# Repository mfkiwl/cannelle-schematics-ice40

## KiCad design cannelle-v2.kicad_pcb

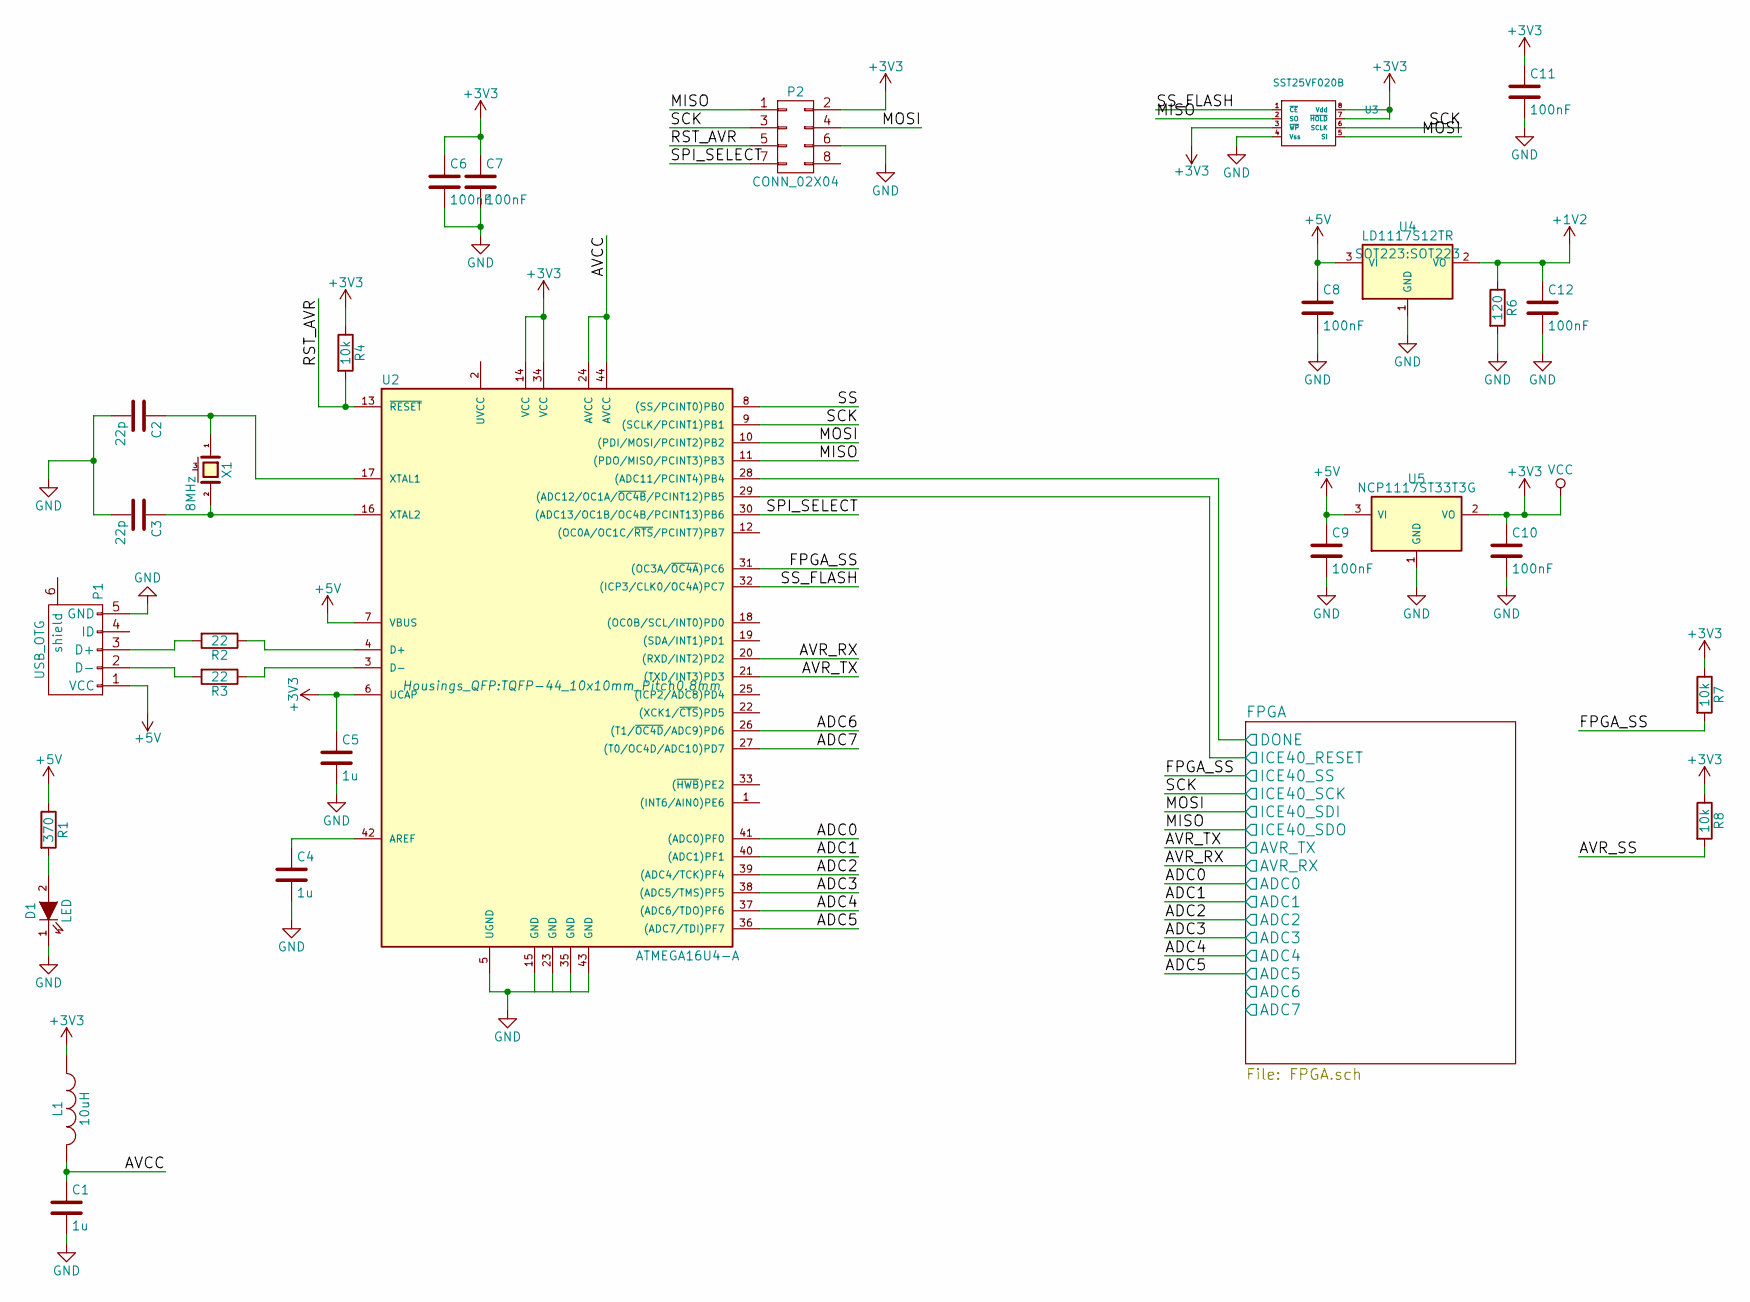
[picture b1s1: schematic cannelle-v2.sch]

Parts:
C1, C4, C5: 1u; C_0402
C2, C3: 22p; C_0402
C6, C7, C8, C9, C10, C11, C12: 100nF; C_0402
D1: LED; C_0603_HandSoldering
L1: 10uH; Neosid_Inductor_SM-NE29_SMD1008
P1: USB_OTG; USB_Mini-B
P2: CONN_02X04; Socket_Strip_Straight_2x04
R1: 370; R_0402
R2, R3: 22; R_0402
R4, R7, R8: 10k; R_0402
R6: 120; R_0402
U2: ATMEGA16U4-A; TQFP-44_10x10mm_Pitch0.8mm
U3: SST25VF020B; SOIC-8-N
U4: LD1117S12TR; SOT223
U5: NCP1117ST33T3G; SOT223
X1: 8MHz; Crystal_HC49-SD_SMD

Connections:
+1V2: C12.1, R6.1, U4.2 (VO); also elsewhere on the board
+3V3: C5.1, C6.1, C7.1, C10.1, C11.1, L1.1, P2.2, R4.1, R7.1, R8.1, U2.6 (UCAP), U2.14 (VCC), U2.34 (VCC), U3.3 (~WP), U3.7 (~HOLD), U3.8 (Vdd), U5.2 (VO); also elsewhere on the board
+5V: C8.1, C9.1, P1.1 (VCC), R1.1, U2.7 (VBUS), U4.3 (VI), U5.3 (VI); also elsewhere on the board
/ADC6: U2.26 ((T1/~OC4D~/ADC9)PD6)
/ADC7: U2.27 ((T0/OC4D/ADC10)PD7)
/AVCC: C1.1, L1.2, U2.24 (AVCC), U2.44 (AVCC)
/AVR_SS: R8.2
/FPGA/ADC0: U2.41 ((ADC0)PF0); also elsewhere on the board
/FPGA/ADC1: U2.40 ((ADC1)PF1); also elsewhere on the board
/FPGA/ADC2: U2.39 ((ADC4/TCK)PF4); also elsewhere on the board
/FPGA/ADC3: U2.38 ((ADC5/TMS)PF5); also elsewhere on the board
/FPGA/ADC4: U2.37 ((ADC6/TDO)PF6); also elsewhere on the board
/FPGA/ADC5: U2.36 ((ADC7/TDI)PF7); also elsewhere on the board
/FPGA/AVR_RX: U2.20 ((RXD/INT2)PD2); also elsewhere on the board
/FPGA/AVR_TX: U2.21 ((TXD/INT3)PD3); also elsewhere on the board
/FPGA/DONE: U2.28 ((ADC11/PCINT4)PB4); also elsewhere on the board
/FPGA/ICE40_RESET: U2.29 ((ADC12/OC1A/~OC4B~/PCINT12)PB5); also elsewhere on the board
/FPGA/ICE40_SCK: P2.3, U2.9 ((SCLK/PCINT1)PB1), U3.6 (SCLK); also elsewhere on the board
/FPGA/ICE40_SDI: P2.4, U2.10 ((PDI/MOSI/PCINT2)PB2), U3.5 (SI); also elsewhere on the board
/FPGA/ICE40_SDO: P2.1, U2.11 ((PDO/MISO/PCINT3)PB3), U3.2 (SO); also elsewhere on the board
/FPGA/ICE40_SS: R7.2, U2.31 ((OC3A/~OC4A~)PC6); also elsewhere on the board
/SPI_SELECT: P2.7, U2.30 ((ADC13/OC1B/OC4B/PCINT13)PB6)
/SS: U2.8 ((SS/PCINT0)PB0)
/SS_FLASH: U2.32 ((ICP3/CLK0/OC4A)PC7), U3.1 (~CE)
GND: C1.2, C2.2, C3.2, C4.2, C5.2, C6.2, C7.2, C8.2, C9.2, C10.2, C11.2, C12.2, D1.1 (K), P1.5 (GND), P2.6, R6.2, U2.5 (UGND), U2.43 (GND), U3.4 (Vss), U4.1 (GND), U5.1 (GND); also elsewhere on the board
unnamed: C2.1, U2.17 (XTAL1), X1.1
unnamed: C3.1, U2.16 (XTAL2), X1.2
unnamed: C4.1, U2.42 (AREF)
unnamed: D1.2 (A), R1.2
unnamed: P1.2 (D-), R3.2
unnamed: P1.3 (D+), R2.2
unnamed: R2.1, U2.4 (D+)
unnamed: R3.1, U2.3 (D-)

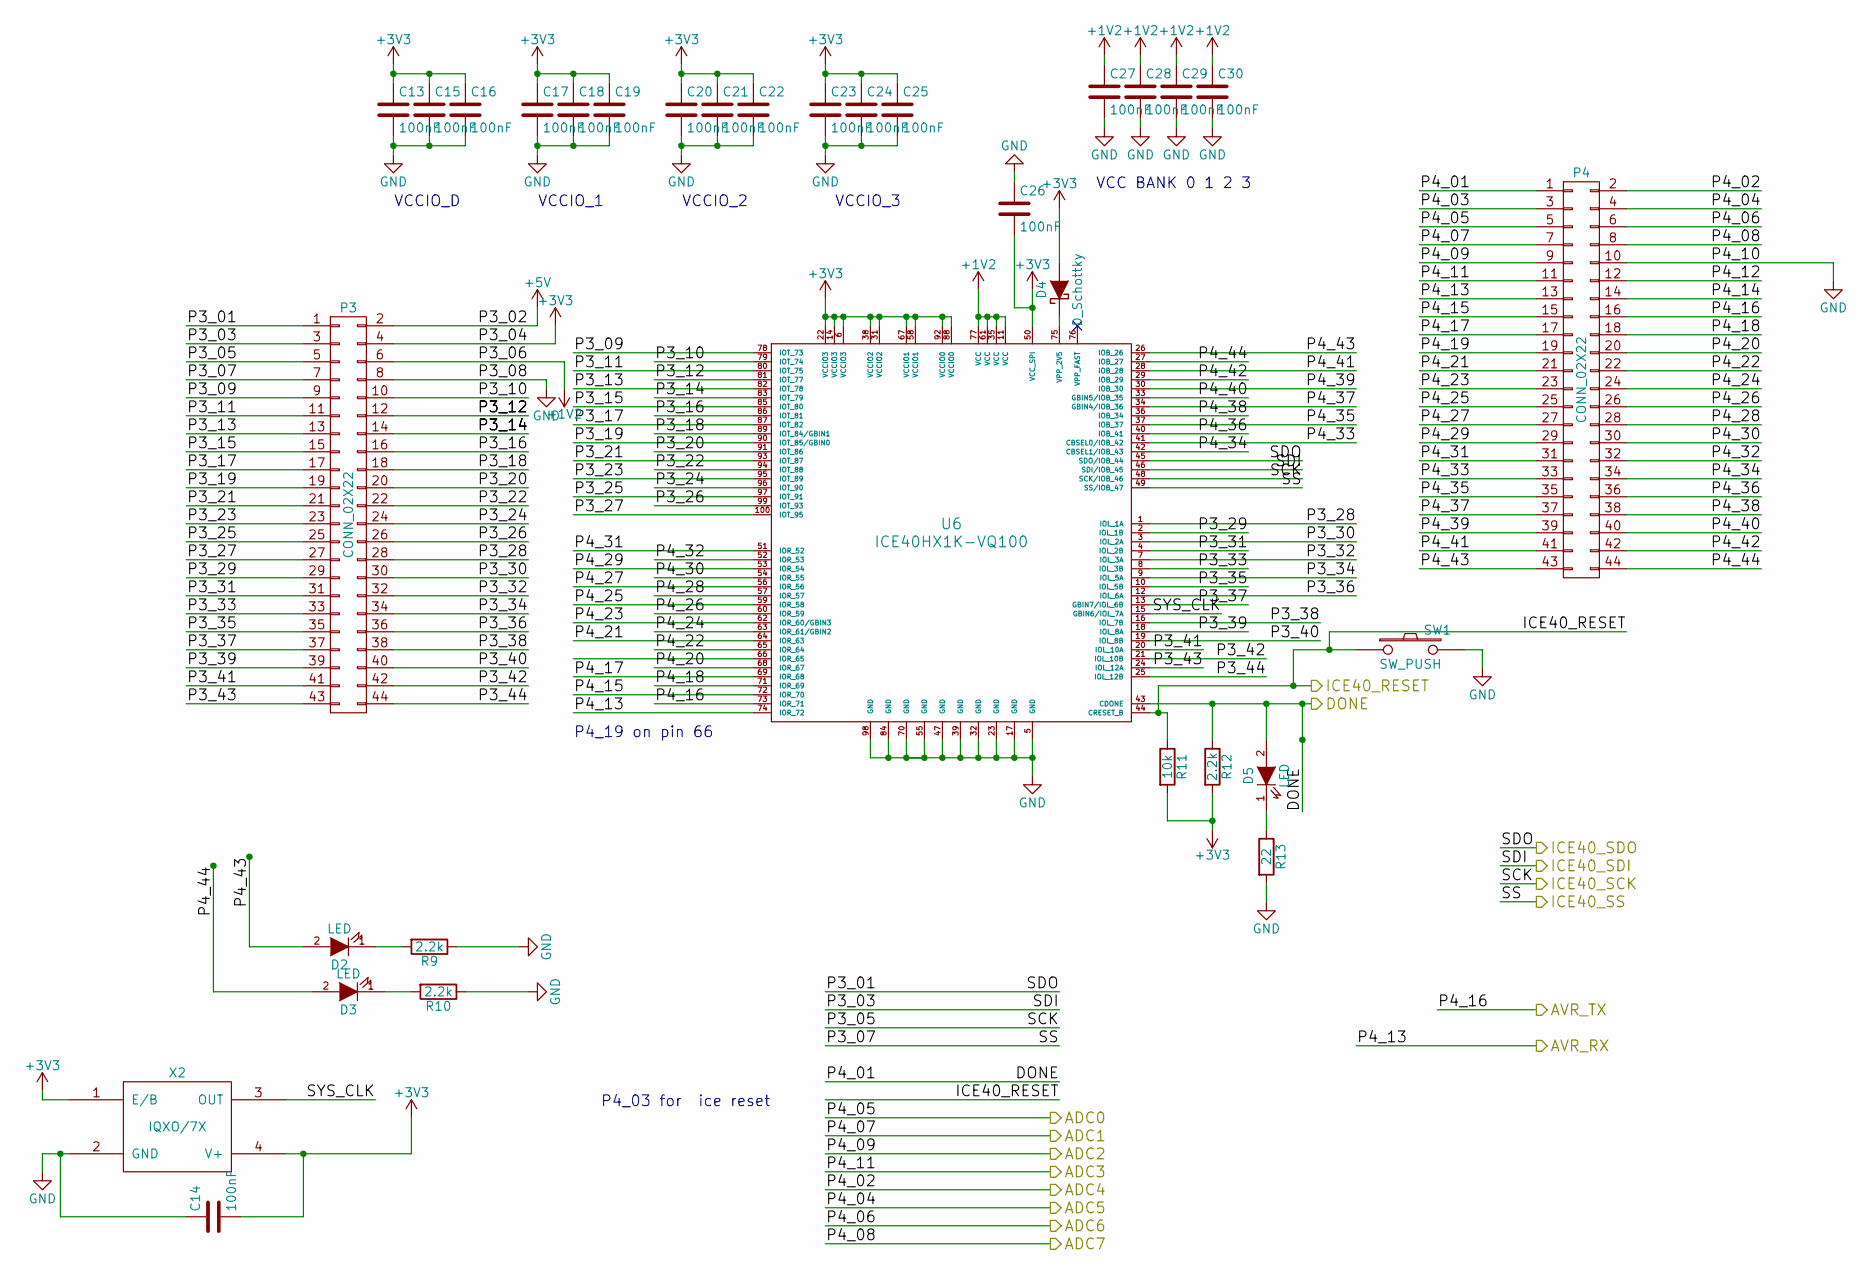
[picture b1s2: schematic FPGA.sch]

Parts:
C13, C14, C15, C16, C17, C18, C19, C20, C21, C22, C23, C24, C25, C26, C27, C28, C29, C30: 100nF; C_0402
D2, D3: LED; C_0603_HandSoldering
D4: D_Schottky; SOD-323
D5: LED; LED_0603
P3, P4: CONN_02X22; Socket_Strip_Straight_2x22
R9, R10, R12: 2.2k; R_0402
R11: 10k; R_0402
R13: 22; R_0402
SW1: SW_PUSH; SW_SPST_PTS645
U6: ICE40HX1K-VQ100; TQFP-100_14x14mm_Pitch0.5mm
X2: IQXO/7X; SI570_SI571_Standard

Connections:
+1V2: C27.1, C28.1, C29.1, C30.1, P3.6, U6.11 (VCC), U6.35 (VCC), U6.61 (VCC), U6.77 (VCC); also elsewhere on the board
+3V3: C13.1, C14.2, C15.1, C16.1, C17.1, C18.1, C19.1, C20.1, C21.1, C22.1, C23.1, C24.1, C25.1, C26.2, D4.2 (A), P3.4, R11.2, R12.2, U6.6 (VCCIO3), U6.14 (VCCIO3), U6.22 (VCCIO3), U6.31 (VCCIO2), U6.38 (VCCIO2), U6.50 (VCC_SPI), U6.58 (VCCIO1), U6.67 (VCCIO1), U6.88 (VCCIO0), U6.92 (VCCIO0), X2.1 (E/B), X2.4 (V+); also elsewhere on the board
+5V: P3.2; also elsewhere on the board
/FPGA/ADC0: P4.5; also elsewhere on the board
/FPGA/ADC1: P4.7; also elsewhere on the board
/FPGA/ADC2: P4.9; also elsewhere on the board
/FPGA/ADC3: P4.11; also elsewhere on the board
/FPGA/ADC4: P4.2; also elsewhere on the board
/FPGA/ADC5: P4.4; also elsewhere on the board
/FPGA/ADC6: P4.6
/FPGA/ADC7: P4.8
/FPGA/AVR_RX: P4.13, U6.74 (IOR_72); also elsewhere on the board
/FPGA/AVR_TX: P4.16, U6.73 (IOR_71); also elsewhere on the board
/FPGA/DONE: D5.2 (A), P4.1, R12.1, U6.43 (CDONE); also elsewhere on the board
/FPGA/ICE40_RESET: R11.1, SW1.1, U6.44 (CRESET_B); also elsewhere on the board
/FPGA/ICE40_SCK: P3.5, U6.48 (SCK/IOB_46); also elsewhere on the board
/FPGA/ICE40_SDI: P3.3, U6.46 (SDI/IOB_45); also elsewhere on the board
/FPGA/ICE40_SDO: P3.1, U6.45 (SDO/IOB_44); also elsewhere on the board
/FPGA/ICE40_SS: P3.7, U6.49 (SS/IOB_47); also elsewhere on the board
/FPGA/P3_09: P3.9, U6.78 (IOT_73)
/FPGA/P3_10: P3.10, U6.79 (IOT_74)
/FPGA/P3_11: P3.11, U6.80 (IOT_75)
/FPGA/P3_12: P3.12, U6.81 (IOT_77)
/FPGA/P3_13: P3.13, U6.82 (IOT_78)
/FPGA/P3_14: P3.14, U6.83 (IOT_79)
/FPGA/P3_15: P3.15, U6.85 (IOT_80)
/FPGA/P3_16: P3.16, U6.86 (IOT_81)
/FPGA/P3_17: P3.17, U6.87 (IOT_82)
/FPGA/P3_18: P3.18, U6.89 (IOT_84/GBIN1)
/FPGA/P3_19: P3.19, U6.90 (IOT_85/GBIN0)
/FPGA/P3_20: P3.20, U6.91 (IOT_86)
/FPGA/P3_21: P3.21, U6.93 (IOT_87)
/FPGA/P3_22: P3.22, U6.94 (IOT_88)
/FPGA/P3_23: P3.23, U6.95 (IOT_89)
/FPGA/P3_24: P3.24, U6.96 (IOT_90)
/FPGA/P3_25: P3.25, U6.97 (IOT_91)
/FPGA/P3_26: P3.26, U6.99 (IOT_93)
/FPGA/P3_27: P3.27, U6.100 (IOT_95)
/FPGA/P3_28: P3.28, U6.1 (IOL_1A)
/FPGA/P3_29: P3.29, U6.2 (IOL_1B)
/FPGA/P3_30: P3.30, U6.3 (IOL_2A)
/FPGA/P3_31: P3.31, U6.4 (IOL_2B)
/FPGA/P3_32: P3.32, U6.7 (IOL_3A)
/FPGA/P3_33: P3.33, U6.8 (IOL_3B)
/FPGA/P3_34: P3.34, U6.9 (IOL_5A)
/FPGA/P3_35: P3.35, U6.10 (IOL_5B)
/FPGA/P3_36: P3.36, U6.12 (IOL_6A)
/FPGA/P3_37: P3.37, U6.13 (GBIN7/IOL_6B)
/FPGA/P3_38: P3.38, U6.16 (IOL_7B)
/FPGA/P3_39: P3.39, U6.18 (IOL_8A)
/FPGA/P3_40: P3.40, U6.19 (IOL_8B)
/FPGA/P3_41: P3.41, U6.20 (IOL_10A)
/FPGA/P3_42: P3.42, U6.21 (IOL_10B)
/FPGA/P3_43: P3.43, U6.24 (IOL_12A)
/FPGA/P3_44: P3.44, U6.25 (IOL_12B)
/FPGA/P4_03: P4.3
/FPGA/P4_12: P4.12
/FPGA/P4_14: P4.14
/FPGA/P4_15: P4.15, U6.72 (IOR_70)
/FPGA/P4_17: P4.17, U6.69 (IOR_68)
/FPGA/P4_18: P4.18, U6.71 (IOR_69)
/FPGA/P4_19: P4.19
/FPGA/P4_20: P4.20, U6.68 (IOR_67)
/FPGA/P4_21: P4.21, U6.64 (IOR_63)
/FPGA/P4_22: P4.22, U6.65 (IOR_64)
/FPGA/P4_23: P4.23, U6.62 (IOR_60/GBIN3)
/FPGA/P4_24: P4.24, U6.63 (IOR_61/GBIN2)
/FPGA/P4_25: P4.25, U6.59 (IOR_58)
/FPGA/P4_26: P4.26, U6.60 (IOR_59)
/FPGA/P4_27: P4.27, U6.56 (IOR_56)
/FPGA/P4_28: P4.28, U6.57 (IOR_57)
/FPGA/P4_29: P4.29, U6.53 (IOR_54)
/FPGA/P4_30: P4.30, U6.54 (IOR_55)
/FPGA/P4_31: P4.31, U6.51 (IOR_52)
/FPGA/P4_32: P4.32, U6.52 (IOR_53)
/FPGA/P4_33: P4.33, U6.41 (CBSEL0/IOB_42)
/FPGA/P4_34: P4.34, U6.42 (CBSEL1/IOB_43)
/FPGA/P4_35: P4.35, U6.37 (IOB_37)
/FPGA/P4_36: P4.36, U6.40 (IOB_41)
/FPGA/P4_37: P4.37, U6.34 (GBIN4/IOB_36)
/FPGA/P4_38: P4.38, U6.36 (IOB_34)
/FPGA/P4_39: P4.39, U6.30 (IOB_30)
/FPGA/P4_40: P4.40, U6.33 (GBIN5/IOB_35)
/FPGA/P4_41: P4.41, U6.28 (IOB_28)
/FPGA/P4_42: P4.42, U6.29 (IOB_29)
/FPGA/P4_43: D2.2 (A), P4.43, U6.26 (IOB_26)
/FPGA/P4_44: D3.2 (A), P4.44, U6.27 (IOB_27)
/FPGA/SYS_CLK: U6.15 (GBIN6/IOL_7A), X2.3 (OUT)
GND: C13.2, C14.1, C15.2, C16.2, C17.2, C18.2, C19.2, C20.2, C21.2, C22.2, C23.2, C24.2, C25.2, C26.1, C27.2, C28.2, C29.2, C30.2, P3.8, P4.10, R9.1, R10.1, R13.2, SW1.2, U6.5 (GND), U6.17 (GND), U6.23 (GND), U6.32 (GND), U6.39 (GND), U6.47 (GND), U6.55 (GND), U6.70 (GND), U6.84 (GND), U6.98 (GND), X2.2 (GND); also elsewhere on the board
unnamed: D2.1 (K), R9.2
unnamed: D3.1 (K), R10.2
unnamed: D4.1 (K), U6.75 (VPP_2V5)
unnamed: D5.1 (K), R13.1

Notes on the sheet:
VCCIO_D
VCCIO_1
VCCIO_2
VCCIO_3
VCC BANK 0 1 2 3
P4_19 on pin 66
P4_03 for ice reset

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
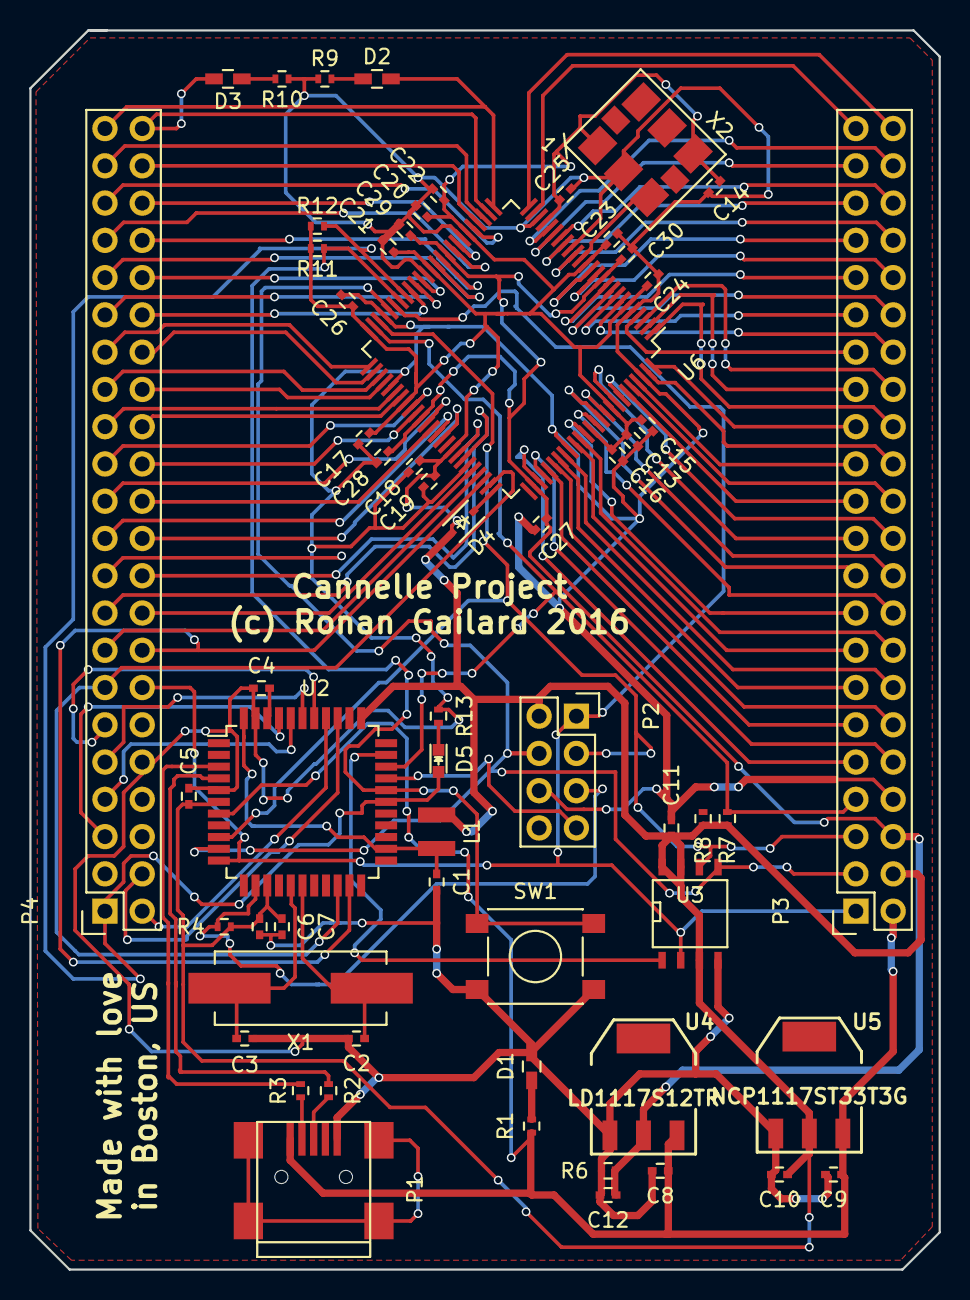
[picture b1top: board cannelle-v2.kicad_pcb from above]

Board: 2 copper layers, 62.0 x 84.5 mm, 60 parts (0 on the bottom side), 99 nets.

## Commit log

2016-07-10 Place components on PCB
2016-07-10 Correct wrong label on schem and PCB
2016-07-10 Ordered labels
2016-07-11 Design first connections on PCB
2016-07-11 Redesign FPGA <-> connectors
2016-07-12 Make AtMega as only SPI Master
2016-07-12 Reorder conectors <-> FPGA
2016-07-12 Change in PCB with new connections
2016-07-12 Add more wires on PCB
2016-07-15 Connect more on PCB and modify the schem a bit
2016-07-15 Connect all pads and edge cuts
2016-07-16 Make some changes before order
